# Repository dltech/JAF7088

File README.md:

# JAF7088
Проект закрыт в связи с неактуальностью, подобраны стандартные номиналы деталей для работы приемника с настройкой от переменного резистора.

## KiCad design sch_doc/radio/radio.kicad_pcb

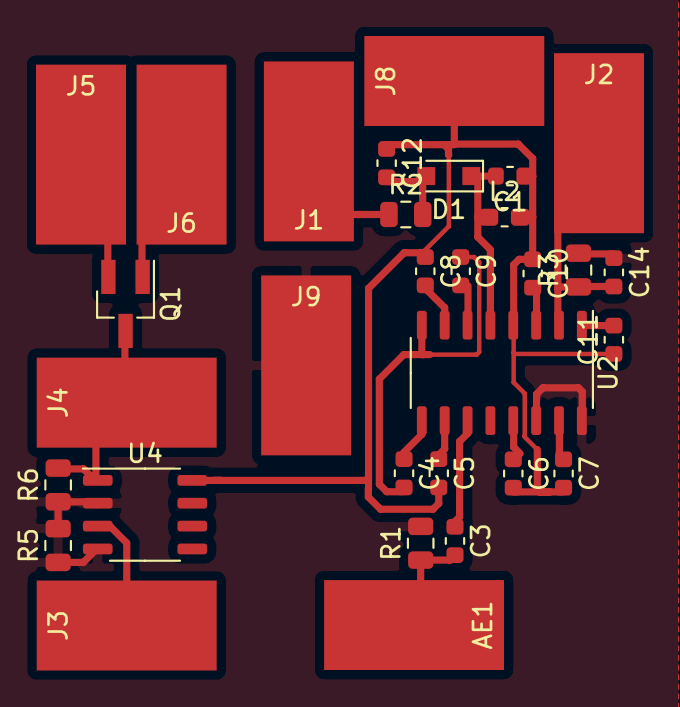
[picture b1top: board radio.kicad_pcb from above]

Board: 2 copper layers, 31 parts (0 on the bottom side), 21 nets.

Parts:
AE1: Antenna; SolderWirePad_1x01_SMD_5x10mm
C1: 100pF; C_0603_1608Metric
C3: 68pF; C_0603_1608Metric
C4: 3.9nF; C_0603_1608Metric
C5, C12: 330pF; C_0603_1608Metric
C6, C11: 0.1uF; C_0603_1608Metric
C7: 470pF; C_0603_1608Metric
C8: 180pF; C_0603_1608Metric
C9: 3.3nF; C_0603_1608Metric
C10: 22nF; C_0603_1608Metric
C14: 1.8nF; C_0603_1608Metric
D1: BB910; D_SOD-323_HandSoldering
J1: tun; SolderWirePad_1x01_SMD_5x10mm
J2, J6: out; SolderWirePad_1x01_SMD_5x10mm
J3: in_op; SolderWirePad_1x01_SMD_5x10mm
J4: in_att; SolderWirePad_1x01_SMD_5x10mm
J5: att; SolderWirePad_1x01_SMD_5x10mm
J8: vcc; SolderWirePad_1x01_SMD_5x10mm
J9: gnd; SolderWirePad_1x01_SMD_5x10mm
L2: 47nH; L_0603_1608Metric_Pad1.05x0.95mm_HandSolder
Q1: AO3400; SOT-23_Handsoldering
R1: 10k; R_0805_2012Metric
R2: 5.6k; R_0805_2012Metric
R3, R5, R6: 22k; R_0805_2012Metric
U2: TDA7088; STC_SOP-16_3.9x9.9mm_P1.27mm
U4: LM358; SOP-8_3.9x4.9mm_P1.27mm

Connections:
+3V3: C1.1, C5.2, C6.2, C7.2, C8.1, C10.1, C11.1, C12.1, J8.1, L2.2, U2.4, U4.8
GND: C14.1, J9.1, R1.2, R3.2, R5.1, R5.2, R6.1, U2.14, U2.16, U4.2, U4.4
unnamed: AE1.1, C3.2, R1.1
unnamed: C1.2, D1.1, L2.1, U2.5
unnamed: C3.1, U2.11
unnamed: C4.1, U2.9
unnamed: C4.2, C9.1, U2.8
unnamed: C5.1, U2.10
unnamed: C6.1, U2.13
unnamed: C7.1, U2.15
unnamed: C8.2, U2.7
unnamed: C9.2, U2.6
unnamed: C10.2, U2.3
unnamed: C11.2, U2.1
unnamed: C12.2, D1.2, R2.2
unnamed: C14.2, J2.1, R3.1, U2.2
unnamed: J1.1, R2.1
unnamed: J3.1, U4.3
unnamed: J4.1, Q1.3, R6.2, U4.1
unnamed: J5.1, Q1.2
unnamed: J6.1, Q1.1

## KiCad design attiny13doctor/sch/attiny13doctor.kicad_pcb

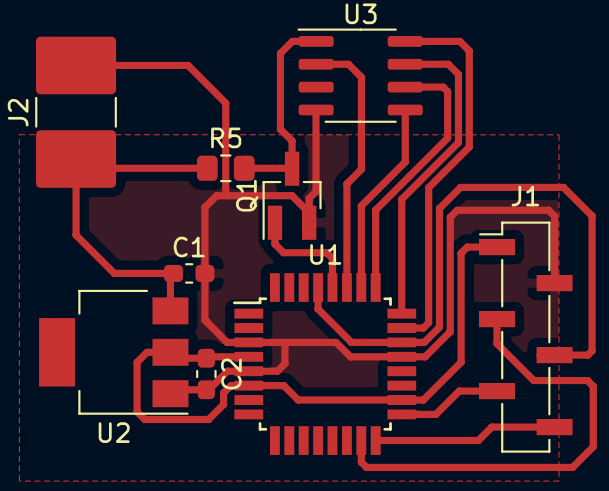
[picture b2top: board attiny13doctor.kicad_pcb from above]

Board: 2 copper layers, 9 parts (0 on the bottom side), 14 nets.

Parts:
C1: 0.1; C_0603_1608Metric_Pad1.05x0.95mm_HandSolder
C2: 0.1uF; C_0603_1608Metric_Pad1.05x0.95mm_HandSolder
J1: programmer_isp; PinSocket_1x06_P2.00mm_Vertical_SMD_Pin1Left
J2: power_supply; C_2816_7142Metric_Pad3.20x4.45mm_HandSolder
Q1: BCR108; SOT-23_Handsoldering
R5: 1k; R_0805_2012Metric_Pad1.15x1.40mm_HandSolder
U1: ATMEGA8A-AU; TQFP-32_7x7mm_P0.8mm
U2: LM1117-5.0; SOT-223
U3: ATTINY13A-SSU; SOIC-8_3.9x4.9mm_P1.27mm

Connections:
+5V: C2.1, J1.1, U1.4, U1.6, U1.18, U2.2
+12V: C1.1, J2.1, R5.1, U2.3
GND: C1.2, C2.2, J1.2, J2.2, Q1.2, U1.3, U1.5, U1.21, U2.1, U3.4
unnamed: J1.3, U1.15
unnamed: J1.4, U1.22, U1.29
unnamed: J1.5, U1.17
unnamed: J1.6, U1.16
unnamed: Q1.1, U1.28
unnamed: Q1.3, R5.2, U3.1
unnamed: U1.23, U3.8
unnamed: U1.24, U3.7
unnamed: U1.25, U3.6
unnamed: U1.26, U3.5
unnamed: U1.27, U3.2

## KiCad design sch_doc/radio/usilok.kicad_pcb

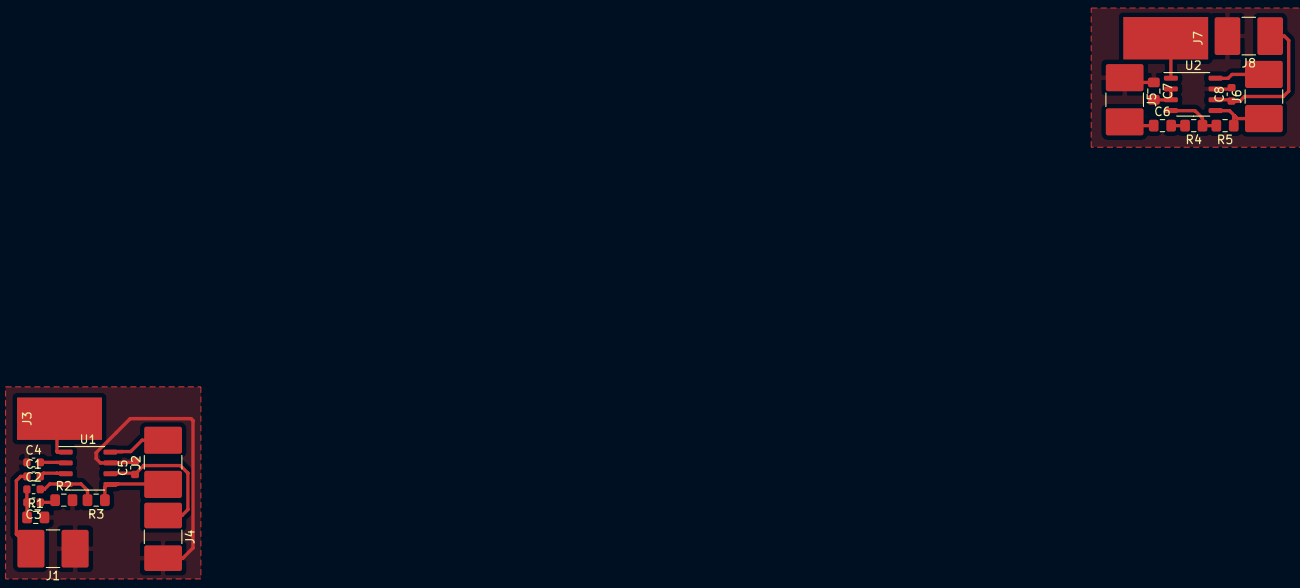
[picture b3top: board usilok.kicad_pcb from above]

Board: 2 copper layers, 23 parts (0 on the bottom side), 18 nets.

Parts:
C1, C5, C8: 0.1uF; C_0603_1608Metric
C2, C3: 0.05uF; C_0603_1608Metric
C4: 5uF; C_0603_1608Metric
C6: 0.5uF; C_0805_2012Metric_Pad1.15x1.40mm_HandSolder
C7: 5uF; C_0805_2012Metric_Pad1.15x1.40mm_HandSolder
J1, J5: in; C_2816_7142Metric_Pad3.20x4.45mm_HandSolder
J2, J6: speaker; C_2816_7142Metric_Pad3.20x4.45mm_HandSolder
J3, J7: mute; SolderWirePad_1x01_SMD_5x10mm
J4, J8: power; C_2816_7142Metric
R1, R2: 22k; R_0805_2012Metric_Pad1.15x1.40mm_HandSolder
R3: 75k; R_0805_2012Metric_Pad1.15x1.40mm_HandSolder
R4, R5: 20k; R_0805_2012Metric_Pad1.15x1.40mm_HandSolder
U1: MC34119; SOP-8_3.9x4.9mm_P1.27mm
U2: MD8002; SOP-8_3.9x4.9mm_P1.27mm

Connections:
+3V3: C5.1, C8.1, J4.1, J8.1, U1.6, U2.6
GND: C4.1, C5.2, C7.1, C8.2, J1.1, J4.2, J5.1, J8.2, R1.2, R2.2, U1.7, U2.7
unnamed: C1.1, J1.2
unnamed: C1.2, U1.3
unnamed: C2.1, C3.2, R1.1
unnamed: C2.2, R3.2, U1.4
unnamed: C3.1, R2.1
unnamed: C4.2, U1.2
unnamed: C6.1, J5.2
unnamed: C6.2, R4.2
unnamed: C7.2, U2.2, U2.3
unnamed: J2.1, R3.1, U1.5
unnamed: J2.2, U1.8
unnamed: J3.1, U1.1
unnamed: J6.1, R5.1, U2.5
unnamed: J6.2, U2.8
unnamed: J7.1, U2.1
unnamed: R4.1, R5.2, U2.4

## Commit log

2020-06-24 проверил только усилитель, все остальное в отладке
2020-07-11 послушал радио с двумя разными усилками и хватит
2022-08-21 indicator and voltage controlled volume regulator added
2022-08-21 schematics ok, but not tested
2022-10-10 pt2313 library element
2022-10-11 new schematics, I hope that it will be final
